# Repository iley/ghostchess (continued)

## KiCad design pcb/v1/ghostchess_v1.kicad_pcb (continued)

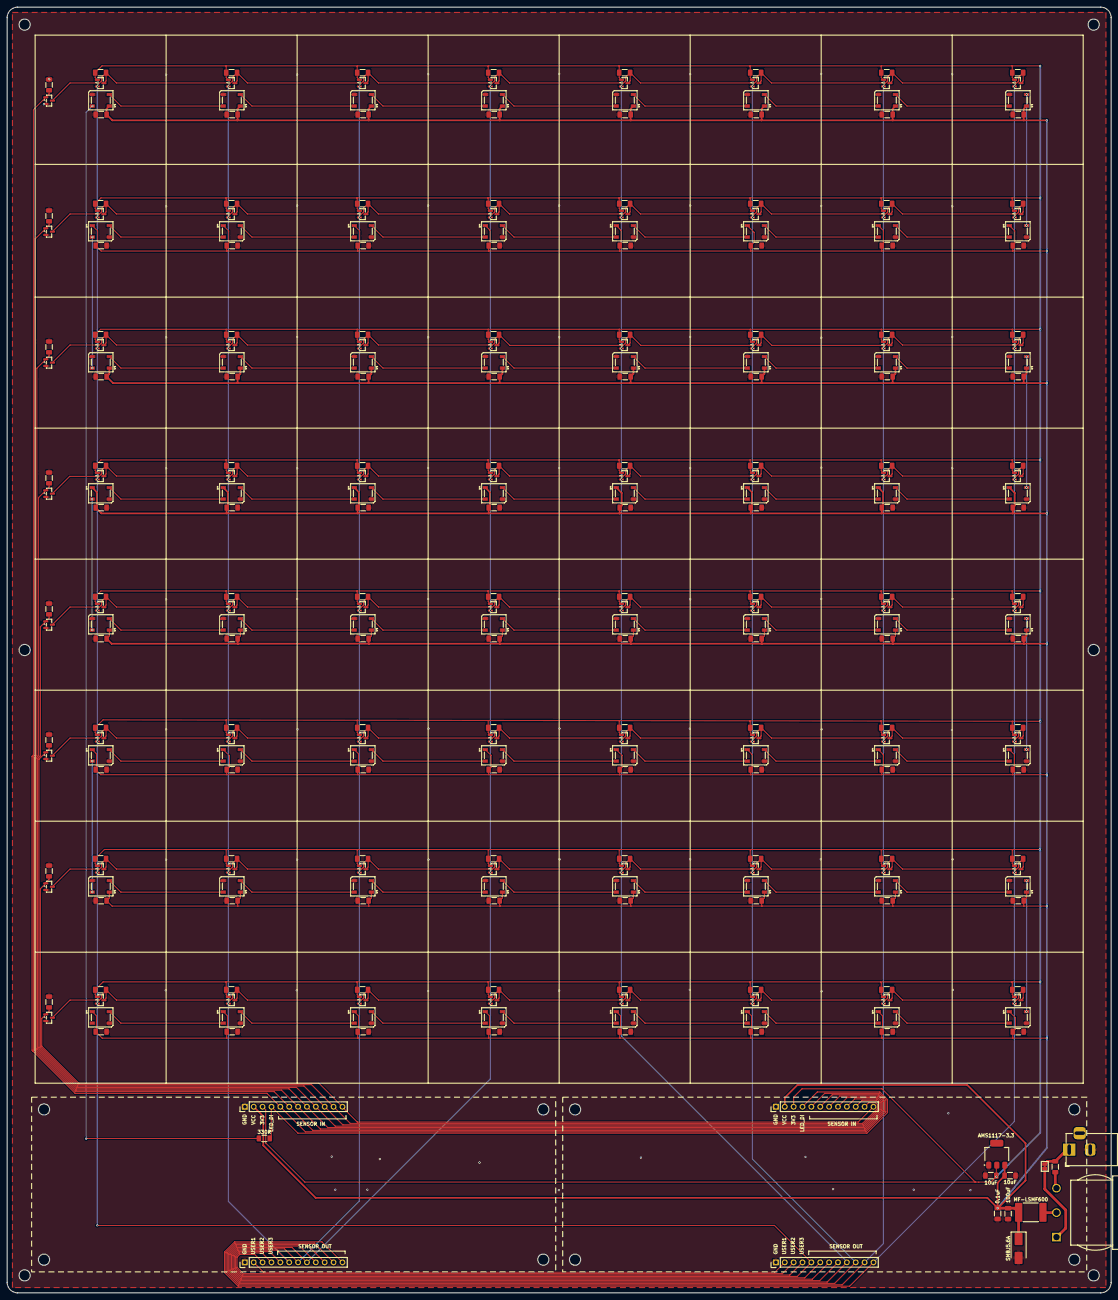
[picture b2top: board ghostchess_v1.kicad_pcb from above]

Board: 2 copper layers, 316.0 x 368.0 mm, 286 parts (0 on the bottom side), 99 nets.

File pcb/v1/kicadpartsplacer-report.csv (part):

Ref,Val,Package,PosX,PosY,Rot,Side
C1,0.1uF,C_1206_3216Metric_Pad1.33x1.80mm_HandSolder,68.9,-72.75,180,top
C2,0.1uF,C_1206_3216Metric_Pad1.33x1.80mm_HandSolder,106.4,-72.75,180,top
C3,0.1uF,C_1206_3216Metric_Pad1.33x1.80mm_HandSolder,143.9,-72.75,180,top
C4,0.1uF,C_1206_3216Metric_Pad1.33x1.80mm_HandSolder,181.4,-72.75,180,top
C5,0.1uF,C_1206_3216Metric_Pad1.33x1.80mm_HandSolder,218.9,-72.75,180,top
C6,0.1uF,C_1206_3216Metric_Pad1.33x1.80mm_HandSolder,256.4,-72.75,180,top
C7,0.1uF,C_1206_3216Metric_Pad1.33x1.80mm_HandSolder,293.9,-72.75,180,top
C8,0.1uF,C_1206_3216Metric_Pad1.33x1.80mm_HandSolder,331.4,-72.75,180,top
C9,0.1uF,C_1206_3216Metric_Pad1.33x1.80mm_HandSolder,68.9,-110.25,0,top
C10,0.1uF,C_1206_3216Metric_Pad1.33x1.80mm_HandSolder,106.4,-110.25,0,top
C11,0.1uF,C_1206_3216Metric_Pad1.33x1.80mm_HandSolder,143.9,-110.25,0,top
C12,0.1uF,C_1206_3216Metric_Pad1.33x1.80mm_HandSolder,181.4,-110.25,0,top
C13,0.1uF,C_1206_3216Metric_Pad1.33x1.80mm_HandSolder,218.9,-110.25,0,top
C14,0.1uF,C_1206_3216Metric_Pad1.33x1.80mm_HandSolder,256.4,-110.25,0,top
C15,0.1uF,C_1206_3216Metric_Pad1.33x1.80mm_HandSolder,293.9,-110.25,0,top
C16,0.1uF,C_1206_3216Metric_Pad1.33x1.80mm_HandSolder,331.4,-110.25,0,top
C17,0.1uF,C_1206_3216Metric_Pad1.33x1.80mm_HandSolder,68.9,-147.75,180,top
C18,0.1uF,C_1206_3216Metric_Pad1.33x1.80mm_HandSolder,106.4,-147.75,180,top
C19,0.1uF,C_1206_3216Metric_Pad1.33x1.80mm_HandSolder,143.9,-147.75,180,top
C20,0.1uF,C_1206_3216Metric_Pad1.33x1.80mm_HandSolder,181.4,-147.75,180,top
C21,0.1uF,C_1206_3216Metric_Pad1.33x1.80mm_HandSolder,218.9,-147.75,180,top
C22,0.1uF,C_1206_3216Metric_Pad1.33x1.80mm_HandSolder,256.4,-147.75,180,top
C23,0.1uF,C_1206_3216Metric_Pad1.33x1.80mm_HandSolder,293.9,-147.75,180,top
C24,0.1uF,C_1206_3216Metric_Pad1.33x1.80mm_HandSolder,331.4,-147.75,180,top
C25,0.1uF,C_1206_3216Metric_Pad1.33x1.80mm_HandSolder,68.9,-185.25,0,top
C26,0.1uF,C_1206_3216Metric_Pad1.33x1.80mm_HandSolder,106.4,-185.25,0,top
C27,0.1uF,C_1206_3216Metric_Pad1.33x1.80mm_HandSolder,143.9,-185.25,0,top
C28,0.1uF,C_1206_3216Metric_Pad1.33x1.80mm_HandSolder,181.4,-185.25,0,top
C29,0.1uF,C_1206_3216Metric_Pad1.33x1.80mm_HandSolder,218.9,-185.25,0,top
C30,0.1uF,C_1206_3216Metric_Pad1.33x1.80mm_HandSolder,256.4,-185.25,0,top
C31,0.1uF,C_1206_3216Metric_Pad1.33x1.80mm_HandSolder,293.9,-185.25,0,top
C32,0.1uF,C_1206_3216Metric_Pad1.33x1.80mm_HandSolder,331.4,-185.25,0,top
C33,0.1uF,C_1206_3216Metric_Pad1.33x1.80mm_HandSolder,68.9,-222.75,180,top
C34,0.1uF,C_1206_3216Metric_Pad1.33x1.80mm_HandSolder,106.4,-222.75,180,top
C35,0.1uF,C_1206_3216Metric_Pad1.33x1.80mm_HandSolder,143.9,-222.75,180,top
C36,0.1uF,C_1206_3216Metric_Pad1.33x1.80mm_HandSolder,181.4,-222.75,180,top
C37,0.1uF,C_1206_3216Metric_Pad1.33x1.80mm_HandSolder,218.9,-222.75,180,top
C38,0.1uF,C_1206_3216Metric_Pad1.33x1.80mm_HandSolder,256.4,-222.75,180,top
C39,0.1uF,C_1206_3216Metric_Pad1.33x1.80mm_HandSolder,293.9,-222.75,180,top
C40,0.1uF,C_1206_3216Metric_Pad1.33x1.80mm_HandSolder,331.4,-222.75,180,top
C41,0.1uF,C_1206_3216Metric_Pad1.33x1.80mm_HandSolder,68.9,-260.25,0,top
C42,0.1uF,C_1206_3216Metric_Pad1.33x1.80mm_HandSolder,106.4,-260.25,0,top
C43,0.1uF,C_1206_3216Metric_Pad1.33x1.80mm_HandSolder,143.9,-260.25,0,top
C44,0.1uF,C_1206_3216Metric_Pad1.33x1.80mm_HandSolder,181.4,-260.25,0,top
C45,0.1uF,C_1206_3216Metric_Pad1.33x1.80mm_HandSolder,218.9,-260.25,0,top
C46,0.1uF,C_1206_3216Metric_Pad1.33x1.80mm_HandSolder,256.4,-260.25,0,top
C47,0.1uF,C_1206_3216Metric_Pad1.33x1.80mm_HandSolder,293.9,-260.25,0,top
C48,0.1uF,C_1206_3216Metric_Pad1.33x1.80mm_HandSolder,331.4,-260.25,0,top
C49,0.1uF,C_1206_3216Metric_Pad1.33x1.80mm_HandSolder,68.9,-297.75,180,top
C50,0.1uF,C_1206_3216Metric_Pad1.33x1.80mm_HandSolder,106.4,-297.75,180,top
C51,0.1uF,C_1206_3216Metric_Pad1.33x1.80mm_HandSolder,143.9,-297.75,180,top
C52,0.1uF,C_1206_3216Metric_Pad1.33x1.80mm_HandSolder,181.4,-297.75,180,top
C53,0.1uF,C_1206_3216Metric_Pad1.33x1.80mm_HandSolder,218.9,-297.75,180,top
C54,0.1uF,C_1206_3216Metric_Pad1.33x1.80mm_HandSolder,256.4,-297.75,180,top
C55,0.1uF,C_1206_3216Metric_Pad1.33x1.80mm_HandSolder,293.9,-297.75,180,top
C56,0.1uF,C_1206_3216Metric_Pad1.33x1.80mm_HandSolder,331.4,-297.75,180,top
C57,0.1uF,C_1206_3216Metric_Pad1.33x1.80mm_HandSolder,68.9,-335.25,0,top
C58,0.1uF,C_1206_3216Metric_Pad1.33x1.80mm_HandSolder,106.4,-335.25,0,top
C59,0.1uF,C_1206_3216Metric_Pad1.33x1.80mm_HandSolder,143.9,-335.25,0,top
C60,0.1uF,C_1206_3216Metric_Pad1.33x1.80mm_HandSolder,181.4,-335.25,0,top
C61,0.1uF,C_1206_3216Metric_Pad1.33x1.80mm_HandSolder,218.9,-335.25,0,top
C62,0.1uF,C_1206_3216Metric_Pad1.33x1.80mm_HandSolder,256.4,-335.25,0,top
C63,0.1uF,C_1206_3216Metric_Pad1.33x1.80mm_HandSolder,293.9,-335.25,0,top
C64,0.1uF,C_1206_3216Metric_Pad1.33x1.80mm_HandSolder,331.4,-335.25,0,top
C65,0.1uF,C_1206_3216Metric_Pad1.33x1.80mm_HandSolder,68.75,-60.75,180,top
C66,0.1uF,C_1206_3216Metric_Pad1.33x1.80mm_HandSolder,106.25,-60.75,0,top
C67,0.1uF,C_1206_3216Metric_Pad1.33x1.80mm_HandSolder,143.75,-60.75,0,top
C68,0.1uF,C_1206_3216Metric_Pad1.33x1.80mm_HandSolder,181.25,-60.75,0,top
C69,0.1uF,C_1206_3216Metric_Pad1.33x1.80mm_HandSolder,218.75,-60.75,0,top
C70,0.1uF,C_1206_3216Metric_Pad1.33x1.80mm_HandSolder,256.25,-60.75,0,top
C71,0.1uF,C_1206_3216Metric_Pad1.33x1.80mm_HandSolder,293.75,-60.75,0,top
C72,0.1uF,C_1206_3216Metric_Pad1.33x1.80mm_HandSolder,331.25,-60.75,0,top
C73,0.1uF,C_1206_3216Metric_Pad1.33x1.80mm_HandSolder,68.75,-98.25,0,top
C74,0.1uF,C_1206_3216Metric_Pad1.33x1.80mm_HandSolder,106.25,-98.25,0,top
C75,0.1uF,C_1206_3216Metric_Pad1.33x1.80mm_HandSolder,143.75,-98.25,0,top
C76,0.1uF,C_1206_3216Metric_Pad1.33x1.80mm_HandSolder,181.25,-98.25,0,top
C77,0.1uF,C_1206_3216Metric_Pad1.33x1.80mm_HandSolder,218.75,-98.25,0,top
C78,0.1uF,C_1206_3216Metric_Pad1.33x1.80mm_HandSolder,256.25,-98.25,0,top
C79,0.1uF,C_1206_3216Metric_Pad1.33x1.80mm_HandSolder,293.75,-98.25,0,top
C80,0.1uF,C_1206_3216Metric_Pad1.33x1.80mm_HandSolder,331.25,-98.25,0,top
C81,0.1uF,C_1206_3216Metric_Pad1.33x1.80mm_HandSolder,68.75,-135.75,0,top
C89,0.1uF,C_1206_3216Metric_Pad1.33x1.80mm_HandSolder,106.25,-135.75,0,top
C83,0.1uF,C_1206_3216Metric_Pad1.33x1.80mm_HandSolder,143.75,-135.75,0,top
C91,0.1uF,C_1206_3216Metric_Pad1.33x1.80mm_HandSolder,181.25,-135.75,0,top
C85,0.1uF,C_1206_3216Metric_Pad1.33x1.80mm_HandSolder,218.75,-135.75,0,top
C93,0.1uF,C_1206_3216Metric_Pad1.33x1.80mm_HandSolder,256.25,-135.75,0,top
C87,0.1uF,C_1206_3216Metric_Pad1.33x1.80mm_HandSolder,293.75,-135.75,0,top
C95,0.1uF,C_1206_3216Metric_Pad1.33x1.80mm_HandSolder,331.25,-135.75,0,top
C82,0.1uF,C_1206_3216Metric_Pad1.33x1.80mm_HandSolder,68.75,-173.25,0,top
C90,0.1uF,C_1206_3216Metric_Pad1.33x1.80mm_HandSolder,106.25,-173.25,0,top
C84,0.1uF,C_1206_3216Metric_Pad1.33x1.80mm_HandSolder,143.75,-173.25,0,top
C92,0.1uF,C_1206_3216Metric_Pad1.33x1.80mm_HandSolder,181.25,-173.25,0,top
C86,0.1uF,C_1206_3216Metric_Pad1.33x1.80mm_HandSolder,218.75,-173.25,0,top
C94,0.1uF,C_1206_3216Metric_Pad1.33x1.80mm_HandSolder,256.25,-173.25,0,top
C88,0.1uF,C_1206_3216Metric_Pad1.33x1.80mm_HandSolder,293.75,-173.25,0,top
C96,0.1uF,C_1206_3216Metric_Pad1.33x1.80mm_HandSolder,331.25,-173.25,0,top
C97,0.1uF,C_1206_3216Metric_Pad1.33x1.80mm_HandSolder,68.75,-210.75,0,top
C105,0.1uF,C_1206_3216Metric_Pad1.33x1.80mm_HandSolder,106.25,-210.75,0,top
C113,0.1uF,C_1206_3216Metric_Pad1.33x1.80mm_HandSolder,143.75,-210.75,0,top
C121,0.1uF,C_1206_3216Metric_Pad1.33x1.80mm_HandSolder,181.25,-210.75,0,top
C101,0.1uF,C_1206_3216Metric_Pad1.33x1.80mm_HandSolder,218.75,-210.75,0,top
C109,0.1uF,C_1206_3216Metric_Pad1.33x1.80mm_HandSolder,256.25,-210.75,0,top
C117,0.1uF,C_1206_3216Metric_Pad1.33x1.80mm_HandSolder,293.75,-210.75,0,top
C125,0.1uF,C_1206_3216Metric_Pad1.33x1.80mm_HandSolder,331.25,-210.75,0,top
C98,0.1uF,C_1206_3216Metric_Pad1.33x1.80mm_HandSolder,68.75,-248.25,0,top
C106,0.1uF,C_1206_3216Metric_Pad1.33x1.80mm_HandSolder,106.25,-248.25,0,top
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
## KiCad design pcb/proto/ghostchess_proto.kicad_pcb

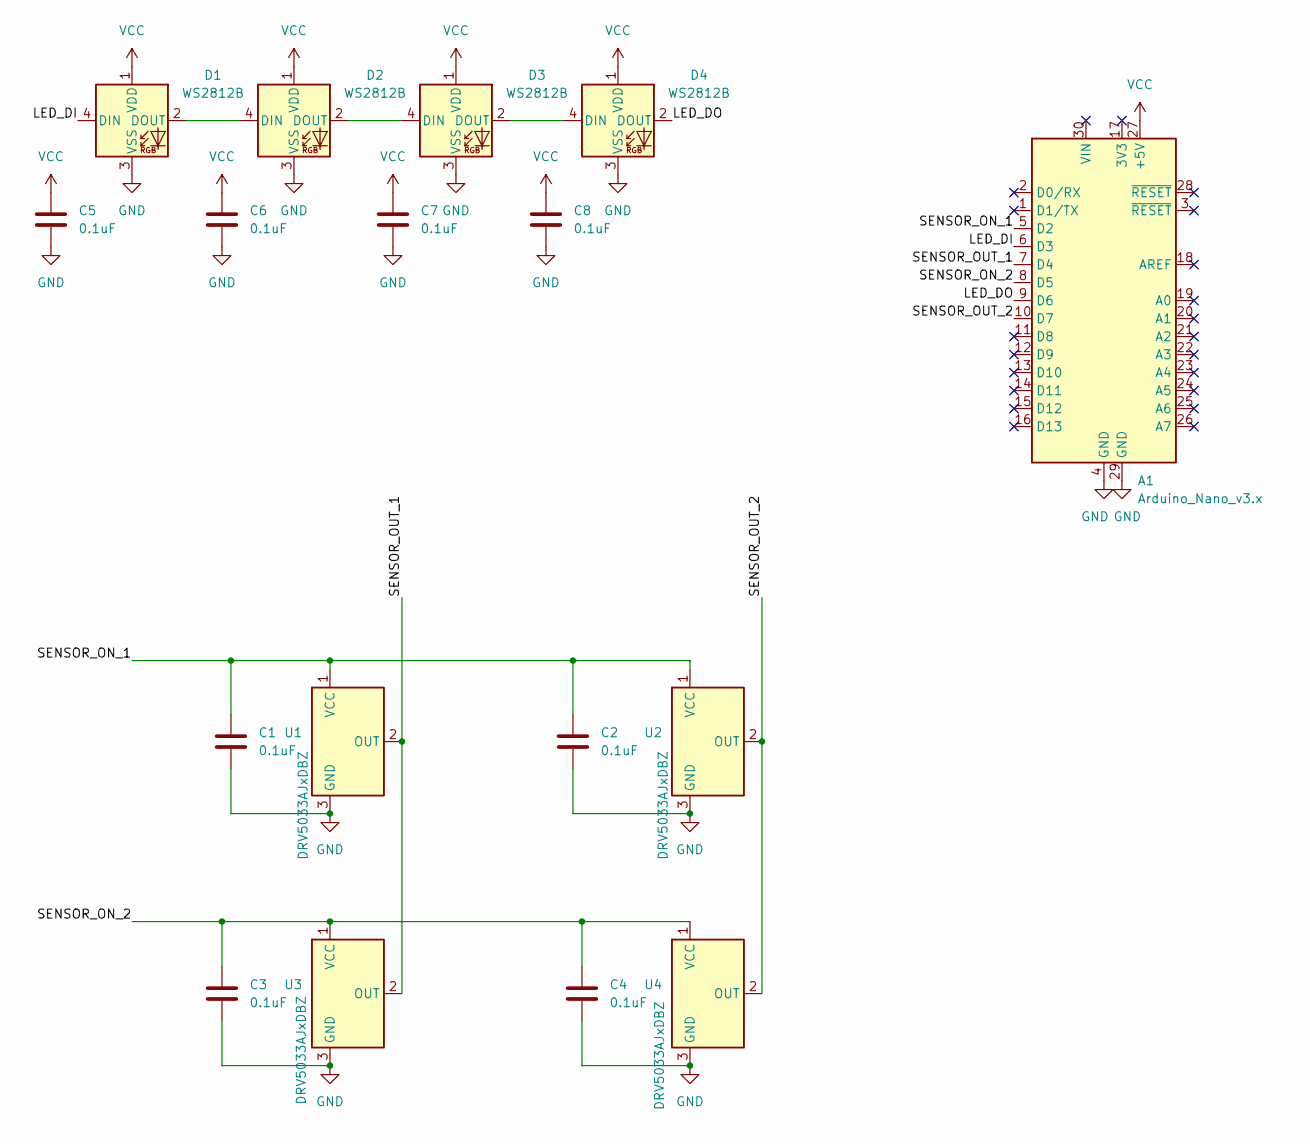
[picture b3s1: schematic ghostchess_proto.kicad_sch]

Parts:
A1: Arduino_Nano_v3.x; Arduino_Nano
C1, C2, C3, C4, C5, C6, C7, C8: 0.1uF; C_0805_2012Metric_Pad1.18x1.45mm_HandSolder
D1, D2, D3, D4: WS2812B; LED_WS2812B_PLCC4_5.0x5.0mm_P3.2mm
U1, U2, U3, U4: DRV5033AJxDBZ; SOT-23

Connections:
/LED_DI: A1.6 (D3), D1.4 (DIN)
/LED_DO: A1.9 (D6), D4.2 (DOUT)
/SENSOR_ON_1: A1.5 (D2), C1.1, C2.1, U1.1 (VCC), U2.1 (VCC)
/SENSOR_ON_2: A1.8 (D5), C3.1, C4.1, U3.1 (VCC), U4.1 (VCC)
/SENSOR_OUT_1: A1.7 (D4), U1.2 (OUT), U3.2 (OUT)
/SENSOR_OUT_2: A1.10 (D7), U2.2 (OUT), U4.2 (OUT)
GND: A1.4 (GND), A1.29 (GND), C1.2, C2.2, C3.2, C4.2, C5.2, C6.2, C7.2, C8.2, D1.3 (VSS), D2.3 (VSS), D3.3 (VSS), D4.3 (VSS), U1.3 (GND), U2.3 (GND), U3.3 (GND), U4.3 (GND)
unnamed: D1.2 (DOUT), D2.4 (DIN)
unnamed: D2.2 (DOUT), D3.4 (DIN)
unnamed: D3.2 (DOUT), D4.4 (DIN)
VCC: A1.27 (+5V), C5.1, C6.1, C7.1, C8.1, D1.1 (VDD), D2.1 (VDD), D3.1 (VDD), D4.1 (VDD)

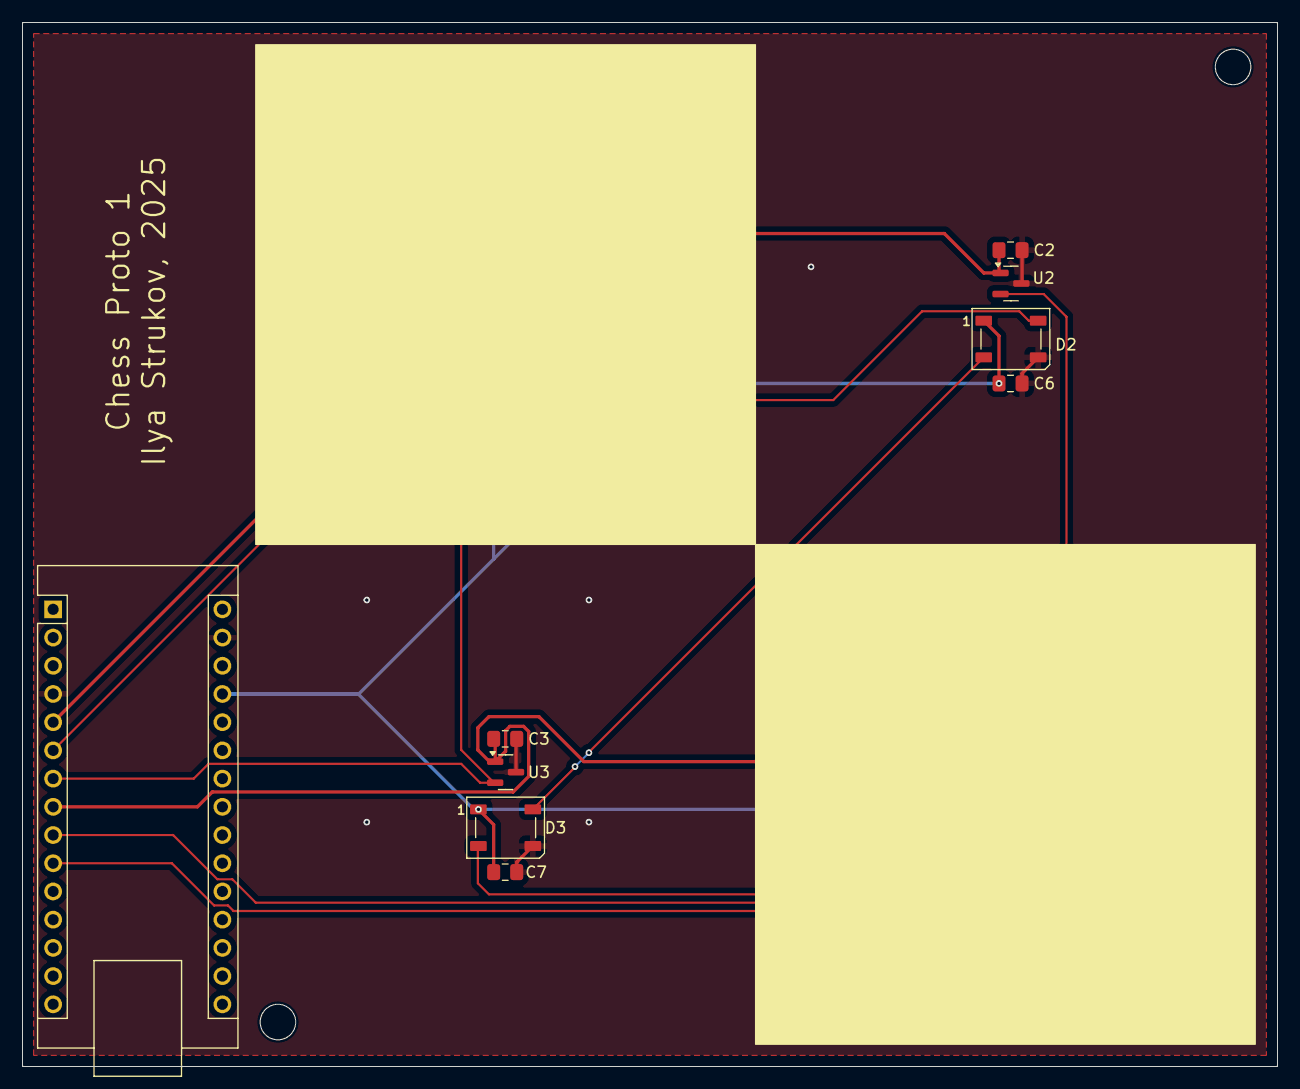
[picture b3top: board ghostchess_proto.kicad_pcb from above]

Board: 2 copper layers, 113.0 x 94.0 mm, 17 parts (0 on the bottom side), 11 nets.

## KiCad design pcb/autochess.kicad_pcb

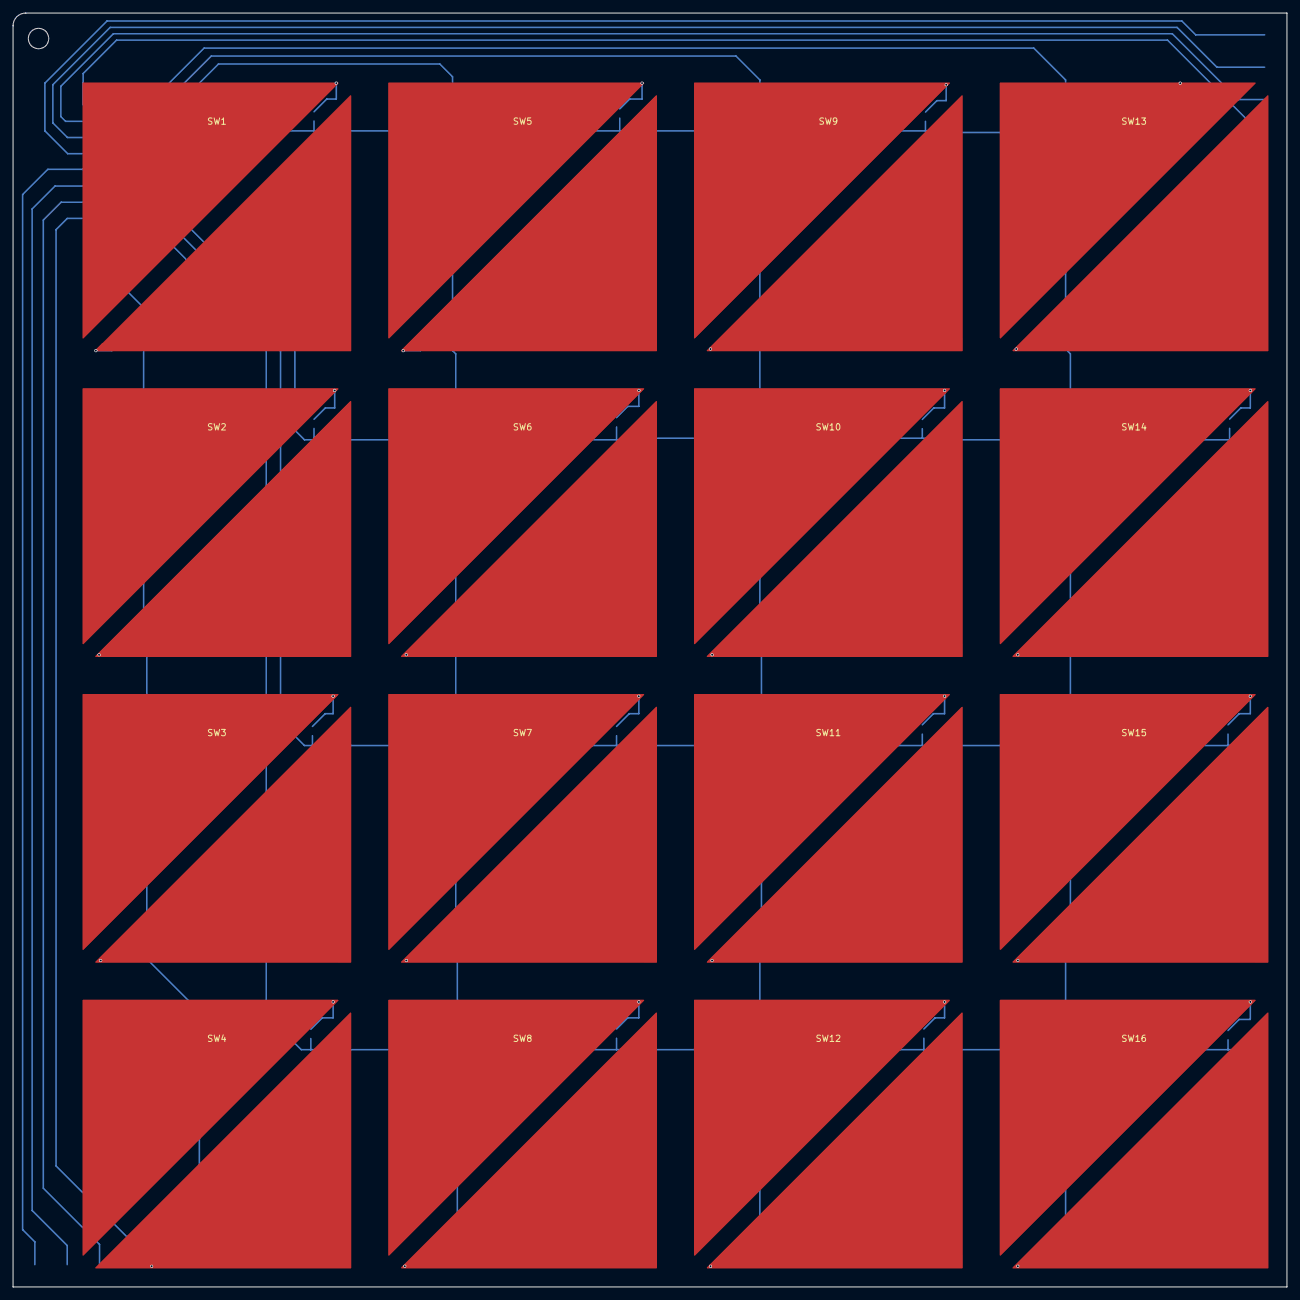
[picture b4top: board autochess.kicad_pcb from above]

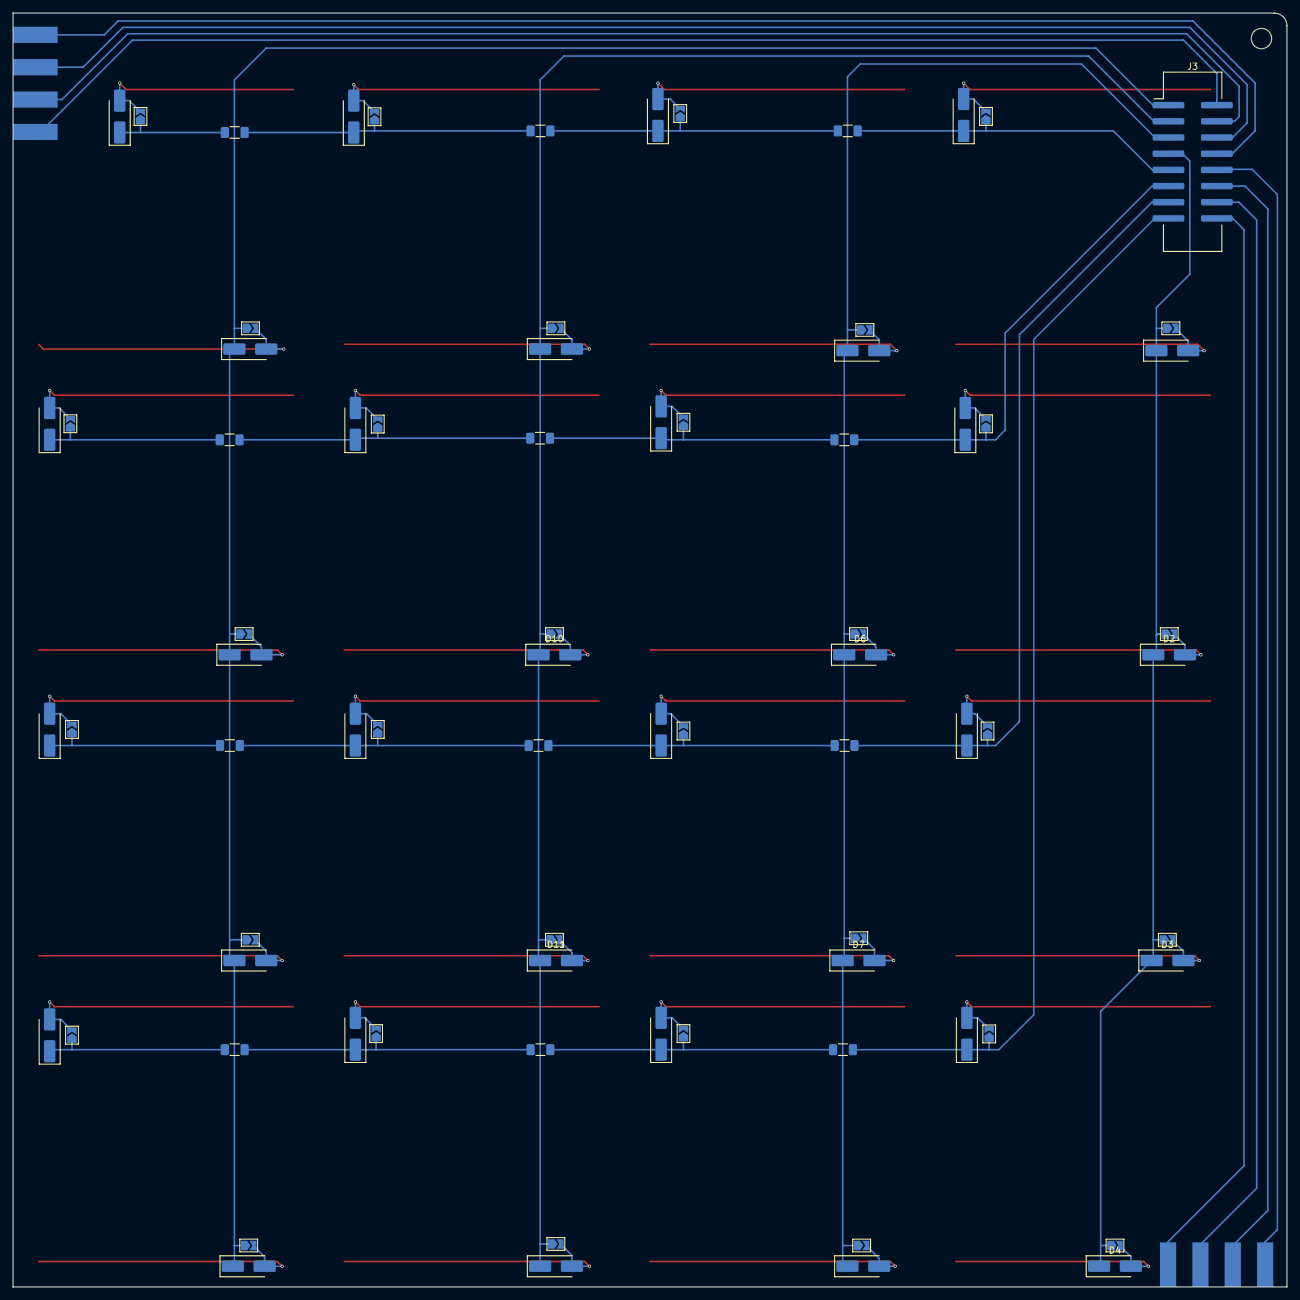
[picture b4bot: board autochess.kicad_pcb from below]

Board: 2 copper layers, 200.0 x 200.0 mm, 95 parts (79 on the bottom side), 60 nets.

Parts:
D1, D2, D3, D4, D5, D6, D7, D8, D9, D10, D11, D12, D13, D14, D15, D16, D17, D18, D19, D20, D21, D22, D23, D24, D25, D26, D27, D28, D29, D30, D31, D32: D; D_SMA_Handsoldering
J1: EDGE_LEFT; Autochess_Edge_Conn_01x04
J2: EDGE_BOT; Autochess_Edge_Conn_01x04
J3: Conn_02x08_Odd_Even; IDC-Header_2x08_P2.54mm_Vertical_SMD
JP1, JP2, JP3, JP4, JP5, JP6, JP7, JP8, JP9, JP10, JP11, JP12, JP13, JP14, JP15, JP16, JP17, JP18, JP19, JP20, JP21, JP22, JP23, JP24, JP25, JP26, JP27, JP28, JP29, JP30, JP31, JP32: SolderJumper-2_P1.3mm_Open_TrianglePad1.0x1.5mm
R1, R2, R3, R4, R5, R6, R7, R8, R9, R10, R11, R12: 0; R_1206_3216Metric_Pad1.30x1.75mm_HandSolder
SW1, SW2, SW3, SW4, SW5, SW6, SW7, SW8, SW9, SW10, SW11, SW12, SW13, SW14, SW15, SW16: SW_Push; Autochess_Square_40mm

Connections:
/COL1: D17.1 (K), J3.9, JP17.1 (A), R10.1
/COL2: D21.1 (K), J3.11, JP21.1 (A), R2.1
/COL3: D25.1 (K), J3.13, JP25.1 (A), R4.1
/COL4: D29.1 (K), J3.15, JP29.1 (A), R8.1
/EXT_COL1: J2.1, J3.16
/EXT_COL2: J2.2, J3.14
/EXT_COL3: J2.3, J3.12
/EXT_COL4: J2.4, J3.10
/EXT_ROW1: J1.4, J3.2
/EXT_ROW2: J1.3, J3.4
/EXT_ROW3: J1.2, J3.6
/EXT_ROW4: J1.1, J3.8
/ROW1: D1.1 (K), D2.1 (K), D3.1 (K), D4.1 (K), J3.7, JP1.1 (A), JP2.1 (A), JP3.1 (A), JP4.1 (A)
/ROW2: D5.1 (K), D6.1 (K), D7.1 (K), D8.1 (K), J3.5, JP5.1 (A), JP6.1 (A), JP7.1 (A), JP8.1 (A)
/ROW3: D9.1 (K), D10.1 (K), D11.1 (K), D12.1 (K), J3.3, JP9.1 (A), JP10.1 (A), JP11.1 (A), JP12.1 (A)
/ROW4: D13.1 (K), D14.1 (K), D15.1 (K), D16.1 (K), J3.1, JP13.1 (A), JP14.1 (A), JP15.1 (A), JP16.1 (A)
unnamed: D1.2 (A), JP1.2 (B), SW1.1
unnamed: D2.2 (A), JP2.2 (B), SW2.1
unnamed: D3.2 (A), JP3.2 (B), SW3.1
unnamed: D4.2 (A), JP4.2 (B), SW4.1
unnamed: D5.2 (A), JP5.2 (B), SW5.1
unnamed: D6.2 (A), JP6.2 (B), SW6.1
unnamed: D7.2 (A), JP7.2 (B), SW7.1
unnamed: D8.2 (A), JP8.2 (B), SW8.1
unnamed: D9.2 (A), JP9.2 (B), SW9.1
unnamed: D10.2 (A), JP10.2 (B), SW10.1
unnamed: D11.2 (A), JP11.2 (B), SW11.1
unnamed: D12.2 (A), JP12.2 (B), SW12.1
unnamed: D13.2 (A), JP13.2 (B), SW13.1
unnamed: D14.2 (A), JP14.2 (B), SW14.1
unnamed: D15.2 (A), JP15.2 (B), SW15.1
unnamed: D16.2 (A), JP16.2 (B), SW16.1
unnamed: D17.2 (A), JP17.2 (B), SW1.2
unnamed: D18.2 (A), JP18.2 (B), SW5.2
unnamed: D18.1 (K), JP18.1 (A), R10.2, R11.1
unnamed: D19.2 (A), JP19.2 (B), SW9.2
unnamed: D19.1 (K), JP19.1 (A), R11.2, R12.1
unnamed: D20.2 (A), JP20.2 (B), SW13.2
unnamed: D20.1 (K), JP20.1 (A), R12.2
unnamed: D21.2 (A), JP21.2 (B), SW2.2
unnamed: D22.2 (A), JP22.2 (B), SW6.2
unnamed: D22.1 (K), JP22.1 (A), R1.1, R2.2
unnamed: D23.2 (A), JP23.2 (B), SW10.2
unnamed: D23.1 (K), JP23.1 (A), R1.2, R3.1
unnamed: D24.2 (A), JP24.2 (B), SW14.2
unnamed: D24.1 (K), JP24.1 (A), R3.2
unnamed: D25.2 (A), JP25.2 (B), SW3.2
unnamed: D26.2 (A), JP26.2 (B), SW7.2
unnamed: D26.1 (K), JP26.1 (A), R4.2, R5.1
unnamed: D27.2 (A), JP27.2 (B), SW11.2
unnamed: D27.1 (K), JP27.1 (A), R5.2, R6.1
unnamed: D28.2 (A), JP28.2 (B), SW15.2
unnamed: D28.1 (K), JP28.1 (A), R6.2
unnamed: D29.2 (A), JP29.2 (B), SW4.2
unnamed: D30.2 (A), JP30.2 (B), SW8.2
unnamed: D30.1 (K), JP30.1 (A), R7.1, R8.2
unnamed: D31.2 (A), JP31.2 (B), SW12.2
unnamed: D31.1 (K), JP31.1 (A), R7.2, R9.1
unnamed: D32.2 (A), JP32.2 (B), SW16.2
unnamed: D32.1 (K), JP32.1 (A), R9.2

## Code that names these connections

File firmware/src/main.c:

#include <avr/interrupt.h>
#include <avr/io.h>
#include <avr/power.h>
#include <stdbool.h>
#include <stdint.h>
#include <util/delay.h>

#include "oled.h"
#include "assistant.h"
#include "buttons.h"

#define BOARD_SIZE 8U
#define LED_COUNT 64U

#define LED_DATA_BIT PB0
#define SENSOR_POWER_ON_MS 2U
#define SENSOR_POWER_OFF_MS 2U
#define SENSOR_SAMPLE_COUNT 8U
#define SENSOR_SAMPLE_INTERVAL_US 100U
#define SENSOR_DEBOUNCE_SCANS 3U
#define BASE_BRIGHTNESS 6U
#define HINT_BRIGHTNESS 48U

#if F_CPU != 11059200UL
#error "The WS2812 timing assumes an 11.0592 MHz CPU clock"
#endif

/* WS2812 byte order on the wire is green, red, blue. */
struct pixel {
    uint8_t green;
    uint8_t red;
    uint8_t blue;
} __attribute__((packed));

static struct pixel pixels[LED_COUNT];
static bool sensor_active[LED_COUNT];
static uint8_t sensor_confidence[LED_COUNT];
static struct assistant game;

/*
 * Send one WS2812 frame on PB0.
 *
 * The inner loop is 14 CPU cycles per bit (1.266 us). A zero stays high for
 * 4 cycles (0.362 us); a one stays high for 9 cycles (0.814 us). Interrupts
 * remain disabled for the approximately 2 ms needed to send all 64 pixels.
 */
static void ws2812_show(const struct pixel *data, uint16_t count)
{
    const uint8_t *bytes = (const uint8_t *)data;
    uint16_t byte_count = count * 3U;
    uint8_t high = PORTB | _BV(LED_DATA_BIT);
    uint8_t low = PORTB & (uint8_t)~_BV(LED_DATA_BIT);
    uint8_t saved_sreg = SREG;

    cli();

    while (byte_count-- != 0U) {
        uint8_t value = *bytes++;
        uint8_t bit_count;

        __asm__ volatile(
            "ldi %[bit_count], 8"        "\n\t"
            "1:"                        "\n\t"
            "out %[port], %[high]"      "\n\t"
            "nop"                       "\n\t"
            "nop"                       "\n\t"
            "sbrs %[value], 7"          "\n\t"
            "out %[port], %[low]"       "\n\t"
            "nop"                       "\n\t"
            "nop"                       "\n\t"
            "nop"                       "\n\t"
            "nop"                       "\n\t"
            "out %[port], %[low]"       "\n\t"
            "lsl %[value]"              "\n\t"
            "dec %[bit_count]"          "\n\t"
            "brne 1b"                   "\n\t"
            : [bit_count] "=&d"(bit_count), [value] "+r"(value)
            : [port] "I"(_SFR_IO_ADDR(PORTB)), [high] "r"(high),
              [low] "r"(low)
            : "cc", "memory");
    }

    SREG = saved_sreg;
    _delay_us(80);
}

/* JTD must be written twice within four CPU cycles. */
static void disable_jtag(void)
{
    uint8_t mcucr = MCUCR | _BV(JTD);

    __asm__ volatile(
        "out %[reg_addr], %[value]" "\n\t"
        "out %[reg_addr], %[value]" "\n\t"
        :
        : [reg_addr] "I"(_SFR_IO_ADDR(MCUCR)), [value] "r"(mcucr)
        : "memory");
}

static void hardware_init(void)
{
    /* Make F_CPU true even when the CKDIV8 fuse is programmed. */
    clock_prescale_set(clock_div_1);

    PORTB &= (uint8_t)~_BV(LED_DATA_BIT);
    DDRB |= _BV(LED_DATA_BIT);

    /* PA0..PA7 are active-low, open-drain sensor inputs. */
    DDRA = 0x00U;
    PORTA = 0xffU;

    /* PC7..PC0 are rank enables. Start with every rank switched off. */
    PORTC = 0x00U;
    disable_jtag();
    DDRC = 0xffU;

    /* Active-low buttons: reset, next choice, confirm. */
    DDRD &= (uint8_t)~(_BV(PD5) | _BV(PD6) | _BV(PD7));
    PORTD |= _BV(PD5) | _BV(PD6) | _BV(PD7);
}

static uint8_t led_index(uint8_t row, uint8_t file)
{
    /* LED data reverses direction on ranks 7, 5, 3, and 1. */
    uint8_t serial_file = ((row & 1U) == 0U) ? file : (7U - file);
    return (uint8_t)(row * BOARD_SIZE + serial_file);
}

/* Poll a free-running timer: LED transmission cannot lose timer interrupts.
 * Timer1 / 256 = 43200 Hz. Read at least once per 1.5-second wrap. */
static uint32_t milliseconds(void)
{
    static uint16_t previous;
    static uint16_t remainder;
    static uint32_t now;
    uint16_t ticks = TCNT1;
    uint16_t elapsed = (uint16_t)(ticks - previous);
    previous = ticks;
    uint32_t scaled = (uint32_t)elapsed * 10U + remainder;
    now += scaled / 432U;
    remainder = scaled % 432U;
    return now;
}

static bool render_board(void)
{
    bool changed = false;
    for (uint8_t row = 0U; row < BOARD_SIZE; ++row) {
        for (uint8_t file = 0U; file < BOARD_SIZE; ++file) {
            uint8_t square = (uint8_t)(row * BOARD_SIZE + file);
            struct pixel *pixel = &pixels[led_index(row, file)];
            struct pixel next = { 0, 0, 0 };
            switch (assistant_light(&game, square)) {
            case LIGHT_WHITE:
                next.red = next.green = next.blue = BASE_BRIGHTNESS;
                break;
            case LIGHT_GREEN: next.green = HINT_BRIGHTNESS / 2U; break;
            case LIGHT_BLUE: next.blue = HINT_BRIGHTNESS; break;
            case LIGHT_ORANGE:
                next.red = HINT_BRIGHTNESS;
                next.green = HINT_BRIGHTNESS / 3U;
                break;
            case LIGHT_RED: next.red = HINT_BRIGHTNESS; break;
            default: break;
            }
            if (pixel->red != next.red || pixel->green != next.green ||
                pixel->blue != next.blue) changed = true;
            *pixel = next;
        }
    }
    return changed;
}

static void scan_sensors(void)
{
    for (uint8_t row = 0U; row < BOARD_SIZE; ++row) {
        /* A low bus before selection still belongs to an earlier row. */
        uint8_t idle_high = PINA;

        /* Row 0 is chess rank 8 / SENSOR_ON_1 / PC7. */
        PORTC = _BV(7U - row);
        _delay_ms(SENSOR_POWER_ON_MS);

        uint8_t detected = (uint8_t)~PINA;

        /* Reject short noise pulses on the weakly pulled-up file buses. */
        for (uint8_t sample = 1U; sample < SENSOR_SAMPLE_COUNT; ++sample) {
            _delay_us(SENSOR_SAMPLE_INTERVAL_US);
            detected &= (uint8_t)~PINA;
        }

        PORTC = 0x00U;

        /* Let the previous row release the shared open-drain file buses. */
        _delay_ms(SENSOR_POWER_OFF_MS);

        for (uint8_t file = 0U; file < BOARD_SIZE; ++file) {
            uint8_t square = (uint8_t)(row * BOARD_SIZE + file);
            bool detected_now = (detected & _BV(file)) != 0U;

            if ((idle_high & _BV(file)) == 0U) {
                continue;
            }

            if (detected_now) {
                if (sensor_confidence[square] < SENSOR_DEBOUNCE_SCANS) {
                    ++sensor_confidence[square];
                }

                if (sensor_confidence[square] == SENSOR_DEBOUNCE_SCANS &&
                    !sensor_active[square]) {
                    sensor_active[square] = true;
                }
            } else {
                if (sensor_confidence[square] > 0U) {
                    --sensor_confidence[square];
                }

                if (sensor_confidence[square] == 0U && sensor_active[square]) {
                    sensor_active[square] = false;
                }
            }
        }
    }
}

int main(void)
{
    hardware_init();
    assistant_init(&game, 0);
    render_board();
    ws2812_show(pixels, LED_COUNT);
    oled_init();

    TCNT1 = 0;
    TCCR1A = 0;
    TCCR1B = _BV(CS12); /* Timer1 prescaler 256. */
    const char *last_status = 0;
    struct buttons buttons = {0};

    for (;;) {
        scan_sensors();
        uint32_t now = milliseconds();
        assistant_update(&game, sensor_active, now);
        buttons_update(&buttons, &game, (uint8_t)(((uint8_t)~PIND >> PD5) & 7U), now);
        if (render_board()) ws2812_show(pixels, LED_COUNT);
        const char *status = assistant_status(&game);
        if (status != last_status) {
            oled_clear();
            oled_write_text(status);
            last_status = status;
        }
    }
}

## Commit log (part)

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2023-07-09 PCB: first attempt
2023-07-09 Remove backup files
2023-07-09 PCB layout: second attempt
2024-11-26 Move older PCB into a subdirectory
2024-11-29 Start proto1 PCB design
2025-01-13 Cleanup
2025-03-29 Proto PCB 1
2025-04-27 Final changes in the Proto PCB
2025-04-27 Proximity sensor test
2025-05-11 LEDs demo
2025-12-06 I dunno
2025-12-25 Make some progress on the PCB
2025-12-25 Update the proto PCB
2026-02-16 Finish the schematic draft, start pcb layout
2026-02-18 Misc. PCB changes
2026-02-21 Continue laying out the PCB
2026-04-04 Continue layout
2026-04-04 Spreasheet-driven layout
2026-04-04 Continue placing component
2026-04-04 Continue placing
2026-04-04 Place most components
2026-04-05 Continue PCB layout
2026-04-05 Add stuff
2026-04-05 s/autochess/ghostchess
2026-04-05 On-off switch 3d model
2026-04-05 Add daughter board symbol
2026-04-05 Daughterboard footprints, more layout work
2026-04-05 Add logo
2026-05-10 More layout
2026-05-10 Fix DRC
2026-05-30 Order the board
2026-06-13 brains pcb start
2026-06-13 OLED demo
2026-06-13 Make progress on the brains PCB
2026-06-14 Start routing
2026-06-27 brains v1 board
